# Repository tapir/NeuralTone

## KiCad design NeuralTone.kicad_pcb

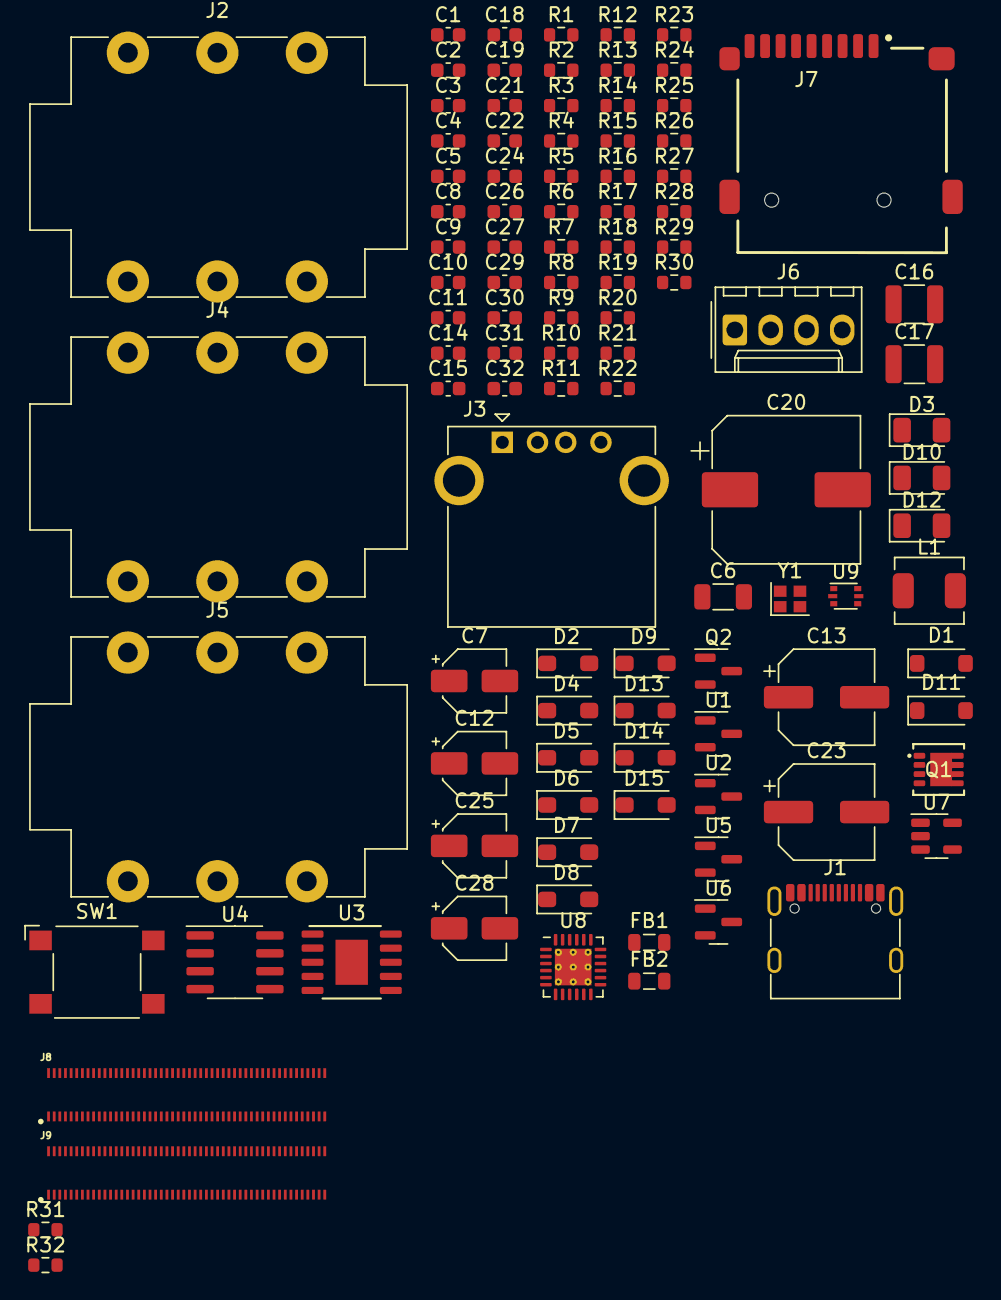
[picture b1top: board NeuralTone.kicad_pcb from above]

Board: 2 copper layers, 104 parts (0 on the bottom side), 74 nets, no tracks yet.

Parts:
C1, C2, C4, C14: 1u; C_0603_1608Metric
C3, C5, C10, C15, C18, C19, C24, C26, C27, C32: 4.7u; C_0603_1608Metric
C6: 100n; C_1206_3216Metric
C7, C12, C25, C28: 10u; CP_Elec_4x5.8
C8, C9, C11, C31: 100n; C_0603_1608Metric
C13, C23: 150u; CP_Elec_6.3x7.7
C16, C17: 47u; C_1210_3225Metric
C20: 2200u; CP_Elec_10x10
C21, C22, C29, C30: 33p; C_0603_1608Metric
D1, D11: 1N4148W; D_SOD-123
D2: SMF9.0A; D_SOD-123F
D3, D10, D12: LED_Small; LED_1206_3216Metric
D4, D5: SMF5.0CA; D_SOD-123F
D6, D7, D8, D9, D13, D14, D15: SMF3.3A; D_SOD-123F
FB1, FB2: BLM21PG220SN1; L_0805_2012Metric
J1: USB-C PD; USB_C_Receptacle_G-Switch_GT-USB-7010ASV
J2: Guitar; Jack_6.35mm_Neutrik_NMJ6HCD2_Horizontal
J3: USB-A Port; USB_A_CONNFLY_DS1095-WNR0
J4: Headphones; Jack_6.35mm_Neutrik_NMJ6HCD2_Horizontal
J5: Line Out; Jack_6.35mm_Neutrik_NMJ6HCD2_Horizontal
J6: 5V Fan; Molex_KK-254_AE-6410-04A_1x04_P2.54mm_Vertical
J7: TF-01A
J8: DF40HC(3.0)-100DS; DF40HC(3.0)-100DS_A
J9: DF40HC(3.0)-100DS; DF40HC(3.0)-100DS_B
L1: 0412CDMCCDS-R10MC; L_Sunlord_MWSA0412S
Q1: AON7421; DMP2008UFG
Q2: IRLML6344; SOT-23
R1, R9, R21, R25, R28: 1k; R_0603_1608Metric
R2: 1.8k; R_0603_1608Metric
R3: 3.9k; R_0603_1608Metric
R4, R11, R19: 470k; R_0603_1608Metric
R5: 2.2M; R_0603_1608Metric
R6, R10, R12, R13, R18, R20, R30: 10k; R_0603_1608Metric
R7, R8: 100m; R_0603_1608Metric
R14, R15, R16, R17, R22, R23, R24, R26, R27, R29: 22; R_0603_1608Metric
R31, R32: 330; R_0603_1608Metric
SW1: SW_Push; SW_SPST_Omron_B3FS-105xP
U1, U6: AP2210N-3.3; SOT-23
U2: AP2210N-5.0; SOT-23
U3: CH224K
U4: MCP6022; SOIC-8_3.9x4.9mm_P1.27mm
U5: AMS1084CM-5.0; SOT-23
U7: AP2171; SOT-23-5
U8: NAU8814YG; QFN-24-1EP_4x4mm_P0.5mm_EP2.6x2.6mm_ThermalVias
U9: USBLC6-2P6; SOT-666
Y1: OT201624MJBA4SL; Crystal_SMD_2016-4Pin_2.0x1.6mm

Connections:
+3.3V: C15.1, C26.1, C27.1, C31.1, C32.1, D9.1 (K), J7.4 (VDD), U6.2 (VO), U8.4 (VDDC), U8.5 (VDDB), Y1.4
+3.3VA: C3.1, C11.2, C18.1, D1.1 (K), R6.2, U1.2 (VO), U4.8 (V+), U8.2 (VDDA)
+5V: C2.1, C13.1, C14.1, C25.1, D11.1 (K), J6.2, J8.77 (+5v_(Input)), J8.79 (+5v_(Input)), J8.81 (+5v_(Input)), J8.83 (+5v_(Input)), J8.85 (+5v_(Input)), J8.87 (+5v_(Input)), R12.1, U1.3 (VI), U5.2 (VO), U6.3 (VI), U7.5 (IN)
+5VA: C5.1, C19.1, U2.2 (VO), U8.20 (VDDSPK)
+9V: C4.1, C12.1, L1.2, R8.1, R9.1, U2.3 (VI), U5.3 (VI)
/HEADPHONES: C20.1, U8.17 (SPKOUT+)
/LINE_OUT: C28.1, U8.16 (MOUT)
/MCLK: U8.11 (MCLK), Y1.3
/PG: R11.2, U3.10 (PG)
/PWM: D11.2 (A), J6.4, Q2.1 (D)
/VBUS: C8.1, D2.1 (K), J1.A9 (VBUS), J1.B9 (VBUS), Q1.1 (S), R1.1
CODEC_AUX: C7.2, R4.1, U8.21 (AUX)
FAN_PWM: J8.38 (GPIO11), R28.1
GND: C1.1, C2.2, C3.2, C4.2, C5.2, C10.1, C11.1, C12.2, C13.2, C14.2, C15.2, C16.2, C17.2, C18.2, C19.2, C21.1, C22.1, C23.2, C24.1, C25.2, C26.2, C27.2, C29.1, C30.1, C31.2, C32.2, D2.2 (A), D3.1 (K), D4.1 (A), D5.1 (A), D6.2 (A), D7.2 (A), D8.2 (A), D9.2 (A), D10.1 (K), D12.1 (K), D13.2 (A), D14.2 (A), D15.2 (A), J1.A12 (GND), J1.B12 (GND), J1.S1 (SHIELD), J2.S, J3.4 (GND), J3.5 (Shield), J4.S, J5.S, J6.1, J7.6 (VSS), J7.9 (SHIELD), J8.1 (GND), J8.2 (GND), J8.7 (GND), J8.8 (GND), J8.13 (GND), J8.14 (GND), J8.22 (GND), J8.23 (GND), J8.32 (GND), J8.33 (GND), J8.42 (GND), J8.43 (GND), J8.52 (GND), J8.53 (GND), J8.59 (GND), J8.60 (GND), J8.65 (GND), J8.66 (GND), J8.71 (GND), J8.74 (GND), J8.98 (GND), J9.107 (GND), J9.108 (GND), J9.113 (GND), J9.114 (GND), J9.119 (GND), J9.120 (GND), J9.125 (GND), J9.126 (GND), J9.131 (GND), J9.132 (GND), J9.137 (GND), J9.138 (GND), J9.144 (GND), J9.150 (GND), J9.155 (GND), J9.156 (GND), J9.161 (GND), J9.162 (GND), J9.167 (GND), J9.168 (GND), J9.173 (GND), J9.174 (GND), J9.179 (GND), J9.180 (GND), J9.185 (GND), J9.186 (GND), J9.191 (GND), J9.192 (GND), J9.197 (GND), J9.198 (GND), Q2.3 (S), R4.2, R10.1, R13.2, R18.2, R19.2, R20.1, R30.2, SW1.2, U1.1 (GND), U2.1 (GND), U3.11 (GND), U4.4 (V-), U5.1 (GND), U6.1 (GND), U7.2 (GND), U8.3 (VSSA), U8.6 (VSSD), U8.18 (VSSSPK), U8.25 (GND), U9.2, Y1.2
I2C_SCL: R31.1, U8.13 (SCLK)
I2C_SDA: R32.1, U8.14 (SDIN)
I2S_BCK: J8.49 (GPIO18), R17.1
I2S_DIN: J8.27 (GPIO20), R15.1
I2S_DOUT: J8.25 (GPIO21), R14.1
I2S_LRCK: J8.26 (GPIO19), R16.1
LED_STAT_1: J8.46 (GPIO22), R21.1
LED_STAT_2: J8.48 (GPIO27), R25.1
MULTI_BTN: J8.50 (GPIO17), SW1.1
unnamed: C6.1, R3.2
unnamed: C16.1, R7.2
unnamed: C17.1, R8.2
unnamed: C20.2, C21.2, FB1.1, R13.1
unnamed: C22.2, D4.2 (A), FB1.2, J4.R, J4.T
unnamed: C28.2, C29.2, FB2.1, R19.1
unnamed: C30.2, D5.2 (A), FB2.2, J5.R, J5.T
unnamed: D1.2 (A), R2.2, R3.1
unnamed: D3.2 (A), R9.2
unnamed: D6.1 (K), J7.1 (DAT2), R22.2
unnamed: D7.1 (K), J7.2 (DAT3/CD), R23.2
unnamed: D8.1 (K), J7.3 (CMD), R24.2
unnamed: D10.2 (A), R21.2
unnamed: D12.2 (A), R25.2
unnamed: D13.1 (K), J7.8 (DAT1), R29.2
unnamed: D14.1 (K), J7.7 (DAT0), R27.2
unnamed: D15.1 (K), J7.5 (CLK), R26.2
unnamed: J1.A5 (CC1), U3.7 (CC1)
unnamed: J1.B5 (CC2), U3.6 (CC2)
unnamed: J2.T, R2.1
unnamed: J3.3 (D+), U9.6
unnamed: J3.2 (D-), U9.4
unnamed: C23.1, J3.1 (VBUS), U7.1 (OUT), U9.5
unnamed: J8.58 (GPIO2), R32.2
unnamed: J8.56 (GPIO3), R31.2
unnamed: J8.78 (GPIO_VREF(1.8v/3.3v_Input)), J8.84 (+3.3v_(Output))
unnamed: C9.1, L1.1, Q1.3 (D), R7.1
unnamed: C8.2, C9.2, Q1.2 (G), R11.1
unnamed: Q2.2 (G), R28.2, R30.1
unnamed: U3.4 (DP), U3.5 (DM)
unnamed: C1.2, R1.2, U3.1 (VDD)
unnamed: C10.2, R6.1, R10.2, U4.3 (+)
unnamed: R5.1, U4.1, U4.2 (-)
unnamed: C6.2, R5.2, U4.5 (+)
unnamed: C7.1, U4.6 (-), U4.7
unnamed: R12.2, U7.4 (EN)
unnamed: R14.2, U8.7 (ADCOUT)
unnamed: R17.2, U8.10 (BCLK)
unnamed: R20.2, U8.12 (CSb/GPIO)
unnamed: R15.2, U8.8 (DACIN)
unnamed: R16.2, U8.9 (FS)
unnamed: R18.1, U8.15 (MODE)
unnamed: C24.2, U8.22 (VREF)
SD_CLK: J8.57 (SD_CLK), R26.1
SD_CMD: J8.62 (SD_CMD), R24.1
SD_DAT0: J8.63 (SD_DAT0), R27.1
SD_DAT1: J8.67 (SD_DAT1), R29.1
SD_DAT2: J8.69 (SD_DAT2), R22.1
SD_DAT3: J8.61 (SD_DAT3), R23.1
USBD+: J9.105 (USB2_P), U9.1
USBD-: J9.103 (USB2_N), U9.3

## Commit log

2023-05-30 increase voltage divider values
2023-05-30 fix resistor value for simulation
2023-05-30 assign initial footprints
2023-05-30 change input cap for current limit switch
2023-05-30 change output cap for current limit switch
2023-05-30 footprint and annotation updates
2023-05-31 footprint adjustments and fixes
2023-05-31 symbol fixes
2023-05-31 update elec cap footprints
2023-05-31 change current limiter cap
2023-05-31 change audio signal film cap to something more available
2023-05-31 rename TVS IC to D
2023-05-31 fix diode number
2023-05-31 redo RPi footprint
2023-05-31 initial 3D files and pcb
2023-06-02 better decoupling strategy
2023-06-02 overall value adjustments
2023-06-04 update to a proper USB PD chip
2023-06-05 better headphone output
2023-06-06 power filter and simulations
2023-06-07 power supply simulations
2023-06-08 psu implementation final
2023-06-09 cleanup and lcsc part numbers
2023-06-11 fan control and other updates
2023-06-11 bleeding resistor change
2023-06-12 stop worrying about coupling caps and be done with it
2023-06-14 more power for output, bigger cap
2023-06-14 fix speaker voltage and current switch diode
2023-06-15 switch power to 9V
2023-06-17 fine tuning before layout
2023-06-18 fix all footprints and 3d models
2023-06-20 increase output cap for regulators
2023-07-13 switch to 0603 footprints
